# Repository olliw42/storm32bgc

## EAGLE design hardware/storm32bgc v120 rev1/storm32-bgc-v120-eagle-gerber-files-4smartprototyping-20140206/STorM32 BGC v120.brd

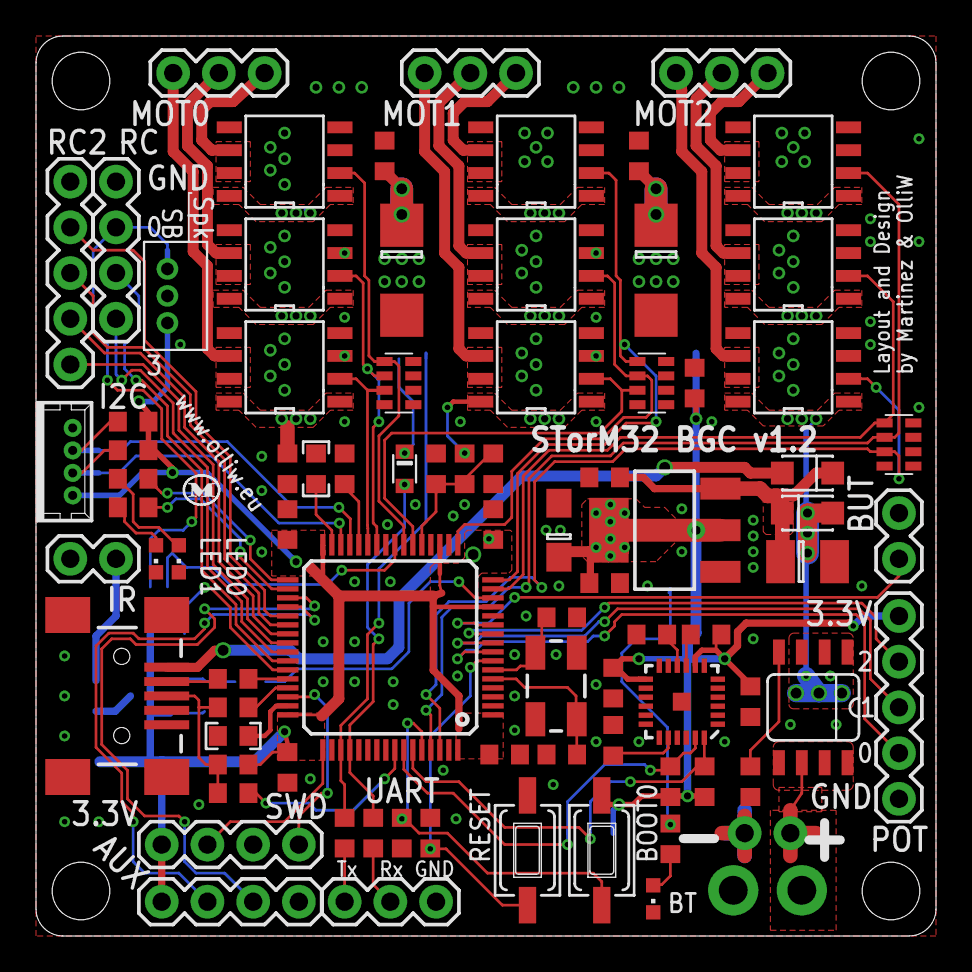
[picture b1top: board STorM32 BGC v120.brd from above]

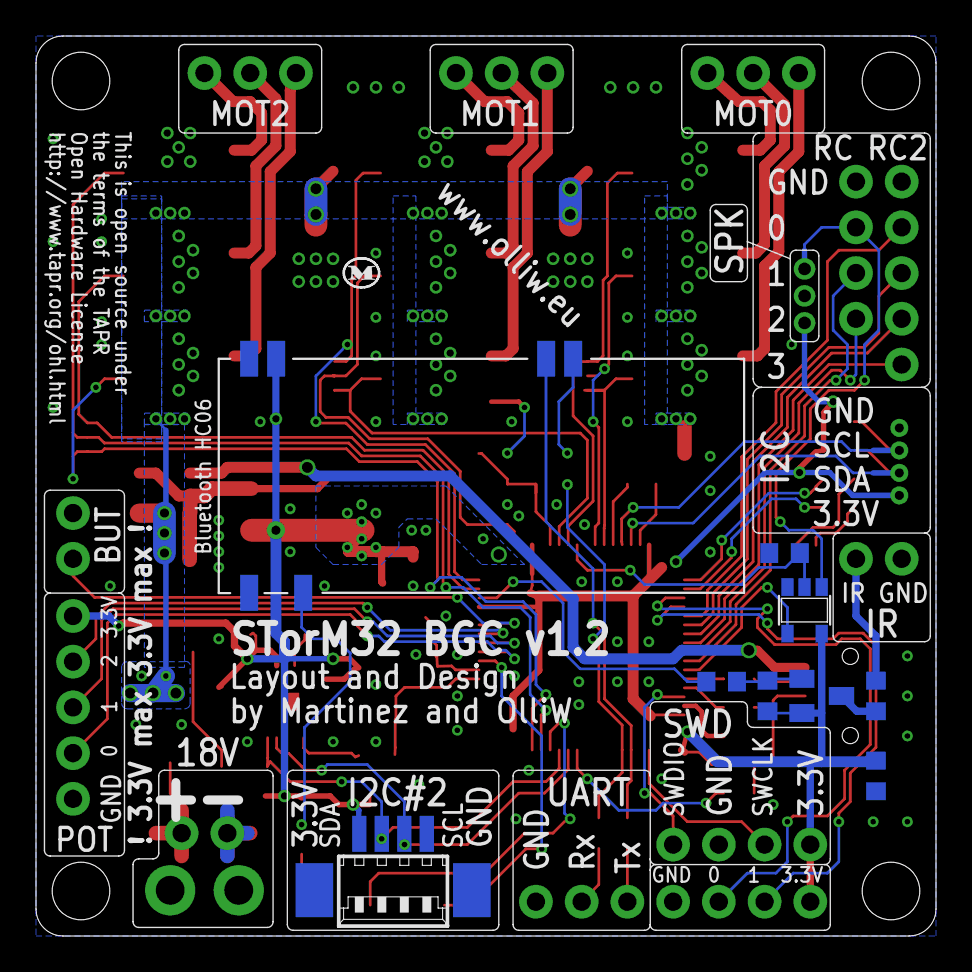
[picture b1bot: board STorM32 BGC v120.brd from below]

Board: 2 copper layers, 50.0 x 50.0 mm, 93 parts (9 on the bottom side), 77 nets.

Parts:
BAT+: 1X1_WITHOUT
BAT-: 1X1_WITHOUT
C1: 10u/20V; SMC_B
C2, C3, C5, C6, C7, C8, C11, C12, C15, C16, C17, C18, C19, C22, C23: 100n; C0603
C4: 10u/6.3V; SMC_A
C9, C10: 22p; C0603
C13, C14: 33u/20V; SMC_C
C20: 10n; C0603
C21: 2.2n; C0603
D1, D2: PMEG3010ER; SOD123W-DIODE
D3: 1PS76SB40; SOD110-R
IC1: STM32F103RCT6; TQFP64
IC2: NCP1117ST33T3G; SOT223
IC3, IC4, IC5, IC6, IC7, IC8, IC9, IC10, IC11: TC4452DFN08; DFN8
IC12: 74AHC1G86DBV; SOT23-5
IC13: MPU6050; QFN-24
IC14: BT HC06; BT_HC05_BASIC
JP1: USBMINIBSMD; USB-MINIB
JP2: MPU-I2C#1; 53047-04SMALL
JP3: SPK; B3B-ZR
JP4: I2C#2; MOLEX-53261-04-SMD-FLAT
JP5: SWD; 1X04
JP6: UART; 1X03
JP7: RC; 1X04
JP8: POT; 1X05
JP9: RC2; 1X05
JP10: BUT; 1X02
JP11: AUX; 1X04
JP12: MOT0; 1X03
JP13: MOT1; 1X03
JP14: MOT2; 1X03
JP15: IR; 1X02
LED1: green; CHIPLED_0603
LED2: red; CHIPLED_0603
LED3: yellow; CHIPLED_0603
Q1: 7B-8.000MAAJ-T; CRYTSAL-SMD-5X3
R1: 47k; R0603
R2, R3, R16, R17, R20: 10k; R0603
R4, R5: 0; R0603
R6: 1k; R0603
R7, R11, R12, R13, R14, R15, R19, R22, R23, R24, R25: 2.2k; R0603
R8, R9: 22; R0603
R10: 150; R0603
R18: 1.5k; R0603
R21: 47; R0603
RN1, RN2, RN3: 10k; CTS742C083
SW1, SW2: SW_TACT_3X6
T1: SI4835DDY; SO08
T2: BCX71HSMD; SOT23

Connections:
3.3V: C3.1, C4.+, C5.1, C6.1, C7.1, C8.1, C18.1, C19.1, C20.1, C23.1, IC1.1, IC1.13, IC1.19, IC1.32, IC1.48, IC1.64, IC2.2, IC2.4, IC12.5, IC13.8, IC13.13, IC14.12, JP2.1, JP3.1, JP4.1, JP5.4, JP8.5, JP11.4, R11.1, R14.2, R15.2, R20.2, R22.2, R23.2, R24.2, SW2.1, T2.2
A0: IC1.27, IC3.2, RN1.3
A1: IC1.22, IC6.2, RN2.3
A2: IC1.62, IC9.2, RN3.3
AUX0: IC1.35, JP11.2
AUX1: IC1.36, JP11.3
B0: IC1.26, IC4.2, RN1.2
B1: IC1.17, IC7.2, RN2.2
B2: IC1.15, IC10.2, RN3.1
BATP: BAT+.1, T1.5, T1.6, T1.7, T1.8
BOOT1: IC1.28, R3.2
BUT: IC1.11, JP10.2
C0: IC1.23, IC5.2, RN1.1
C1: IC1.16, IC8.2, RN2.1
C2: IC1.61, IC11.2, RN3.2
GND: BAT-.1, C1.-, C2.2, C3.2, C4.-, C5.2, C6.2, C7.2, C8.2, C9.1, C10.1, C11.2, C12.2, C13.-, C14.-, C15.2, C16.2, C17.2, C18.2, C19.2, C20.2, C21.2, C22.2, C23.2, IC1.12, IC1.18, IC1.63, IC2.1, IC3.3, IC3.4, IC3.5, IC4.3, IC4.4, IC4.5, IC5.3, IC5.4, IC5.5, IC6.3, IC6.4, IC6.5, IC7.3, IC7.4, IC7.5, IC8.3, IC8.4, IC8.5, IC9.3, IC9.4, IC9.5, IC10.3, IC10.4, IC10.5, IC11.3, IC11.4, IC11.5, IC12.3, IC13.1, IC13.11, IC13.18, IC14.13, IC14.22, JP1.GND, JP2.4, JP3.2, JP4.4, JP5.2, JP6.1, JP7.1, JP8.1, JP9.1, JP10.1, JP11.1, JP15.1, LED1.C, LED2.C, LED3.C, Q1.2, Q1.4, R1.2, R2.2, R3.1, R4.1, R5.1, R16.1, R18.1, RN1.5, RN1.6, RN1.7, RN1.8, RN2.5, RN2.6, RN2.7, RN2.8, RN3.5, RN3.6, RN3.7, RN3.8, SW1.2
IR: IC1.14, R19.1
LED0: IC1.33, R6.1
LED1: IC1.34, R7.1
LIPO: C12.1, IC1.21, R17.2, R18.2
M0A: IC3.6, IC3.7, JP12.1
M0B: IC4.6, IC4.7, JP12.2
M0C: IC5.6, IC5.7, JP12.3
M1A: IC6.6, IC6.7, JP13.1
M1B: IC7.6, IC7.7, JP13.2
M1C: IC8.6, IC8.7, JP13.3
M2A: IC9.6, IC9.7, JP14.1
M2B: IC10.6, IC10.7, JP14.2
M2C: IC11.6, IC11.7, JP14.3
unnamed: R21.1, T2.3
unnamed: JP15.2, R21.2
unnamed: C11.1, IC1.7, SW1.1
unnamed: IC1.60, R2.1, SW2.2
unnamed: LED1.A, R6.2
unnamed: LED2.A, R7.2
unnamed: IC1.47, R5.2
unnamed: C9.2, IC1.5, Q1.3
unnamed: C10.2, IC1.6, Q1.1
unnamed: JP1.D-, R8.1
unnamed: JP1.D+, R9.1, R10.1, R11.2
unnamed: IC13.9, R22.1
unnamed: C22.1, IC13.10
unnamed: IC14.24, R25.1
unnamed: LED3.A, R25.2
unnamed: R1.1, T1.4
unnamed: C21.1, IC13.20
unnamed: D3.C, IC14.1
unnamed: IC1.31, R4.2
unnamed: R19.2, R20.1, T2.1
unnamed: JP6.2, R13.2
unnamed: JP6.3, R12.2
POT0: IC1.8, JP8.2
POT1: IC1.9, JP8.3
POT2: IC1.10, JP8.4
RC0-IN: IC12.1, JP3.3, JP7.2
RC0/RX: IC1.43, IC12.4
RC1/TX: IC1.42, JP7.3
RC2: IC1.41, JP7.4
RC2-0: IC1.37, JP9.2
RC2-1: IC1.38, JP9.3
RC2-2: IC1.39, JP9.4
RC2-3: IC1.40, JP9.5
RX: D3.A, IC1.52, R13.1
SCL: IC1.29, JP2.3, R14.1
SCL#2: IC1.58, IC13.23, JP4.3, R23.1
SDA: IC1.30, JP2.2, R15.1
SDA#2: IC1.59, IC13.24, JP4.2, R24.1
SWCLK: IC1.49, JP5.3
SWDIO: IC1.46, JP5.1
TX: IC1.51, IC14.2, R12.1
USB-D: IC1.57, R10.2
USB-DM: IC1.44, R8.2
USB-DP: IC1.45, R9.2
VCC: C13.+, C14.+, C15.1, C16.1, C17.1, D1.A, IC3.1, IC3.8, IC4.1, IC4.8, IC5.1, IC5.8, IC6.1, IC6.8, IC7.1, IC7.8, IC8.1, IC8.8, IC9.1, IC9.8, IC10.1, IC10.8, IC11.1, IC11.8, R17.1, T1.1, T1.2, T1.3
VIN: C1.+, C2.1, D1.C, D2.C, IC2.3
VUSB: D2.A, JP1.VBUS
XOR: IC1.24, IC12.2, R16.2

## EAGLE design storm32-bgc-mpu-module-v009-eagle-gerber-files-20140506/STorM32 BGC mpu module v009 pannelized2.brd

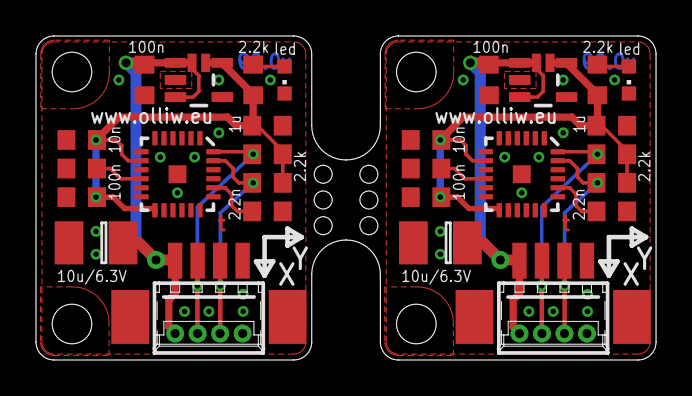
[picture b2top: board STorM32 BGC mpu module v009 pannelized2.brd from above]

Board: 2 copper layers, 34.4 x 18.0 mm, 30 parts (0 on the bottom side), 16 nets.

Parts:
C1, C8: 10u/6.3V; SMC_B
C2, C3, C6, C9, C12, C13: 100n; C0603
C4, C10: 10n; C0603
C5, C11: 2.2n; C0603
C7, C14: 1u; C0603
IC1, IC3: MPU6050; QFN-24
IC2, IC4: SOT23-5
JP1, JP2: I2C#2; MOLEX-53261-04-SMD-BOTH
LED1, LED2: red; CHIPLED_0603
R1, R2, R3, R4, R5, R6: 2.2k; R0603
SJ1, SJ2: SOLDERJUMPERNO; SJ_2S-NO

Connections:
3.3V: C3.1, C4.1, C7.1, IC1.8, IC1.13, IC2.5, R1.1, R2.2, R3.2, SJ1.2
3.3V1: C10.1, C12.1, C14.1, IC3.8, IC3.13, IC4.5, R4.2, R5.2, R6.1, SJ2.2
5V: C1.+, C2.1, IC2.1, IC2.3, JP1.1, JP1.5, SJ1.1
5V1: C8.+, C13.1, IC4.1, IC4.3, JP2.1, JP2.5, SJ2.1
GND: C1.-, C2.2, C3.2, C4.2, C5.2, C6.2, C7.2, IC1.1, IC1.9, IC1.11, IC1.18, IC2.2, IC2.4, JP1.4, JP1.8, LED1.C
GND4: C8.-, C9.2, C10.2, C11.2, C12.2, C13.2, C14.2, IC3.1, IC3.9, IC3.11, IC3.18, IC4.2, IC4.4, JP2.4, JP2.8, LED2.C
unnamed: LED2.A, R6.2
unnamed: C9.1, IC3.10
unnamed: C11.1, IC3.20
unnamed: LED1.A, R1.2
unnamed: C6.1, IC1.10
unnamed: C5.1, IC1.20
SCL: IC1.23, JP1.3, JP1.7, R2.1
SCL1: IC3.23, JP2.3, JP2.7, R4.1
SDA: IC1.24, JP1.2, JP1.6, R3.1
SDA1: IC3.24, JP2.2, JP2.6, R5.1

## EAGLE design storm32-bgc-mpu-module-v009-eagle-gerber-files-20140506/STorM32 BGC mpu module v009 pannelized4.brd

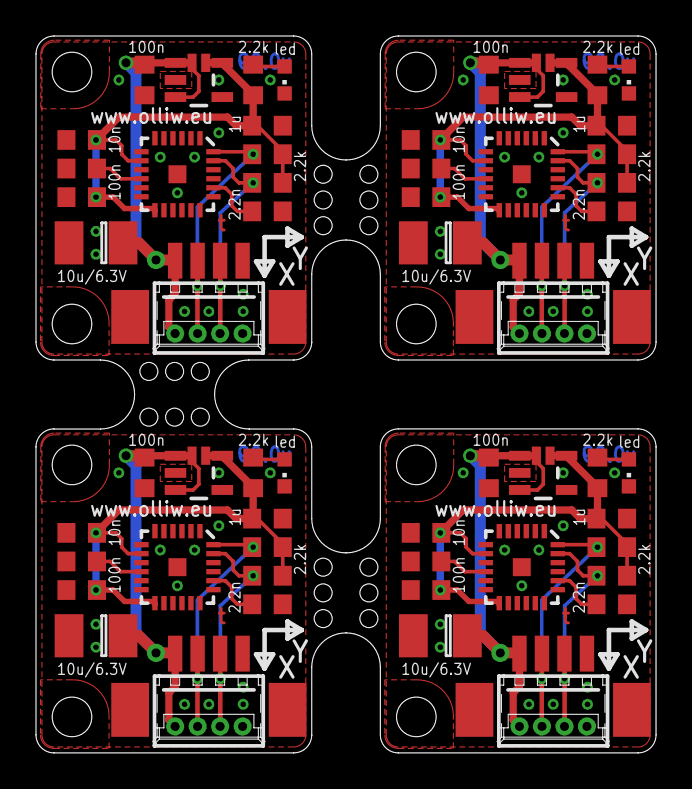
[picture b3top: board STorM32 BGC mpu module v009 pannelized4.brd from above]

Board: 2 copper layers, 34.4 x 39.8 mm, 60 parts (0 on the bottom side), 32 nets.

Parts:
C1, C8, C15, C22: 10u/6.3V; SMC_B
C2, C3, C6, C9, C12, C13, C16, C19, C20, C23, C26, C27: 100n; C0603
C4, C10, C17, C24: 10n; C0603
C5, C11, C18, C25: 2.2n; C0603
C7, C14, C21, C28: 1u; C0603
IC1, IC3, IC5, IC7: MPU6050; QFN-24
IC2, IC4, IC6, IC8: SOT23-5
JP1, JP2, JP3, JP4: I2C#2; MOLEX-53261-04-SMD-BOTH
LED1, LED2, LED3, LED4: red; CHIPLED_0603
R1, R2, R3, R4, R5, R6, R7, R8, R9, R10, R11, R12: 2.2k; R0603
SJ1, SJ2, SJ3, SJ4: SOLDERJUMPERNO; SJ_2S-NO

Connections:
3.3V: C3.1, C4.1, C7.1, IC1.8, IC1.13, IC2.5, R1.1, R2.2, R3.2, SJ1.2
3.3V1: C10.1, C12.1, C14.1, IC3.8, IC3.13, IC4.5, R4.2, R5.2, R6.1, SJ2.2
3.3V2: C17.1, C19.1, C21.1, IC5.8, IC5.13, IC6.5, R7.2, R8.2, R9.1, SJ3.2
3.3V3: C24.1, C26.1, C28.1, IC7.8, IC7.13, IC8.5, R10.2, R11.2, R12.1, SJ4.2
5V: C1.+, C2.1, IC2.1, IC2.3, JP1.1, JP1.5, SJ1.1
5V1: C8.+, C13.1, IC4.1, IC4.3, JP2.1, JP2.5, SJ2.1
5V2: C15.+, C20.1, IC6.1, IC6.3, JP3.1, JP3.5, SJ3.1
5V3: C22.+, C27.1, IC8.1, IC8.3, JP4.1, JP4.5, SJ4.1
GND: C1.-, C2.2, C3.2, C4.2, C5.2, C6.2, C7.2, IC1.1, IC1.9, IC1.11, IC1.18, IC2.2, IC2.4, JP1.4, JP1.8, LED1.C
GND4: C8.-, C9.2, C10.2, C11.2, C12.2, C13.2, C14.2, IC3.1, IC3.9, IC3.11, IC3.18, IC4.2, IC4.4, JP2.4, JP2.8, LED2.C
GND5: C15.-, C16.2, C17.2, C18.2, C19.2, C20.2, C21.2, IC5.1, IC5.9, IC5.11, IC5.18, IC6.2, IC6.4, JP3.4, JP3.8, LED3.C
GND6: C22.-, C23.2, C24.2, C25.2, C26.2, C27.2, C28.2, IC7.1, IC7.9, IC7.11, IC7.18, IC8.2, IC8.4, JP4.4, JP4.8, LED4.C
unnamed: LED2.A, R6.2
unnamed: C9.1, IC3.10
unnamed: C11.1, IC3.20
unnamed: LED3.A, R9.2
unnamed: C16.1, IC5.10
unnamed: C18.1, IC5.20
unnamed: LED4.A, R12.2
unnamed: C23.1, IC7.10
unnamed: LED1.A, R1.2
unnamed: C25.1, IC7.20
unnamed: C6.1, IC1.10
unnamed: C5.1, IC1.20
SCL: IC1.23, JP1.3, JP1.7, R2.1
SCL1: IC3.23, JP2.3, JP2.7, R4.1
SCL2: IC5.23, JP3.3, JP3.7, R7.1
SCL3: IC7.23, JP4.3, JP4.7, R10.1
SDA: IC1.24, JP1.2, JP1.6, R3.1
SDA1: IC3.24, JP2.2, JP2.6, R5.1
SDA2: IC5.24, JP3.2, JP3.6, R8.1
SDA3: IC7.24, JP4.2, JP4.6, R11.1

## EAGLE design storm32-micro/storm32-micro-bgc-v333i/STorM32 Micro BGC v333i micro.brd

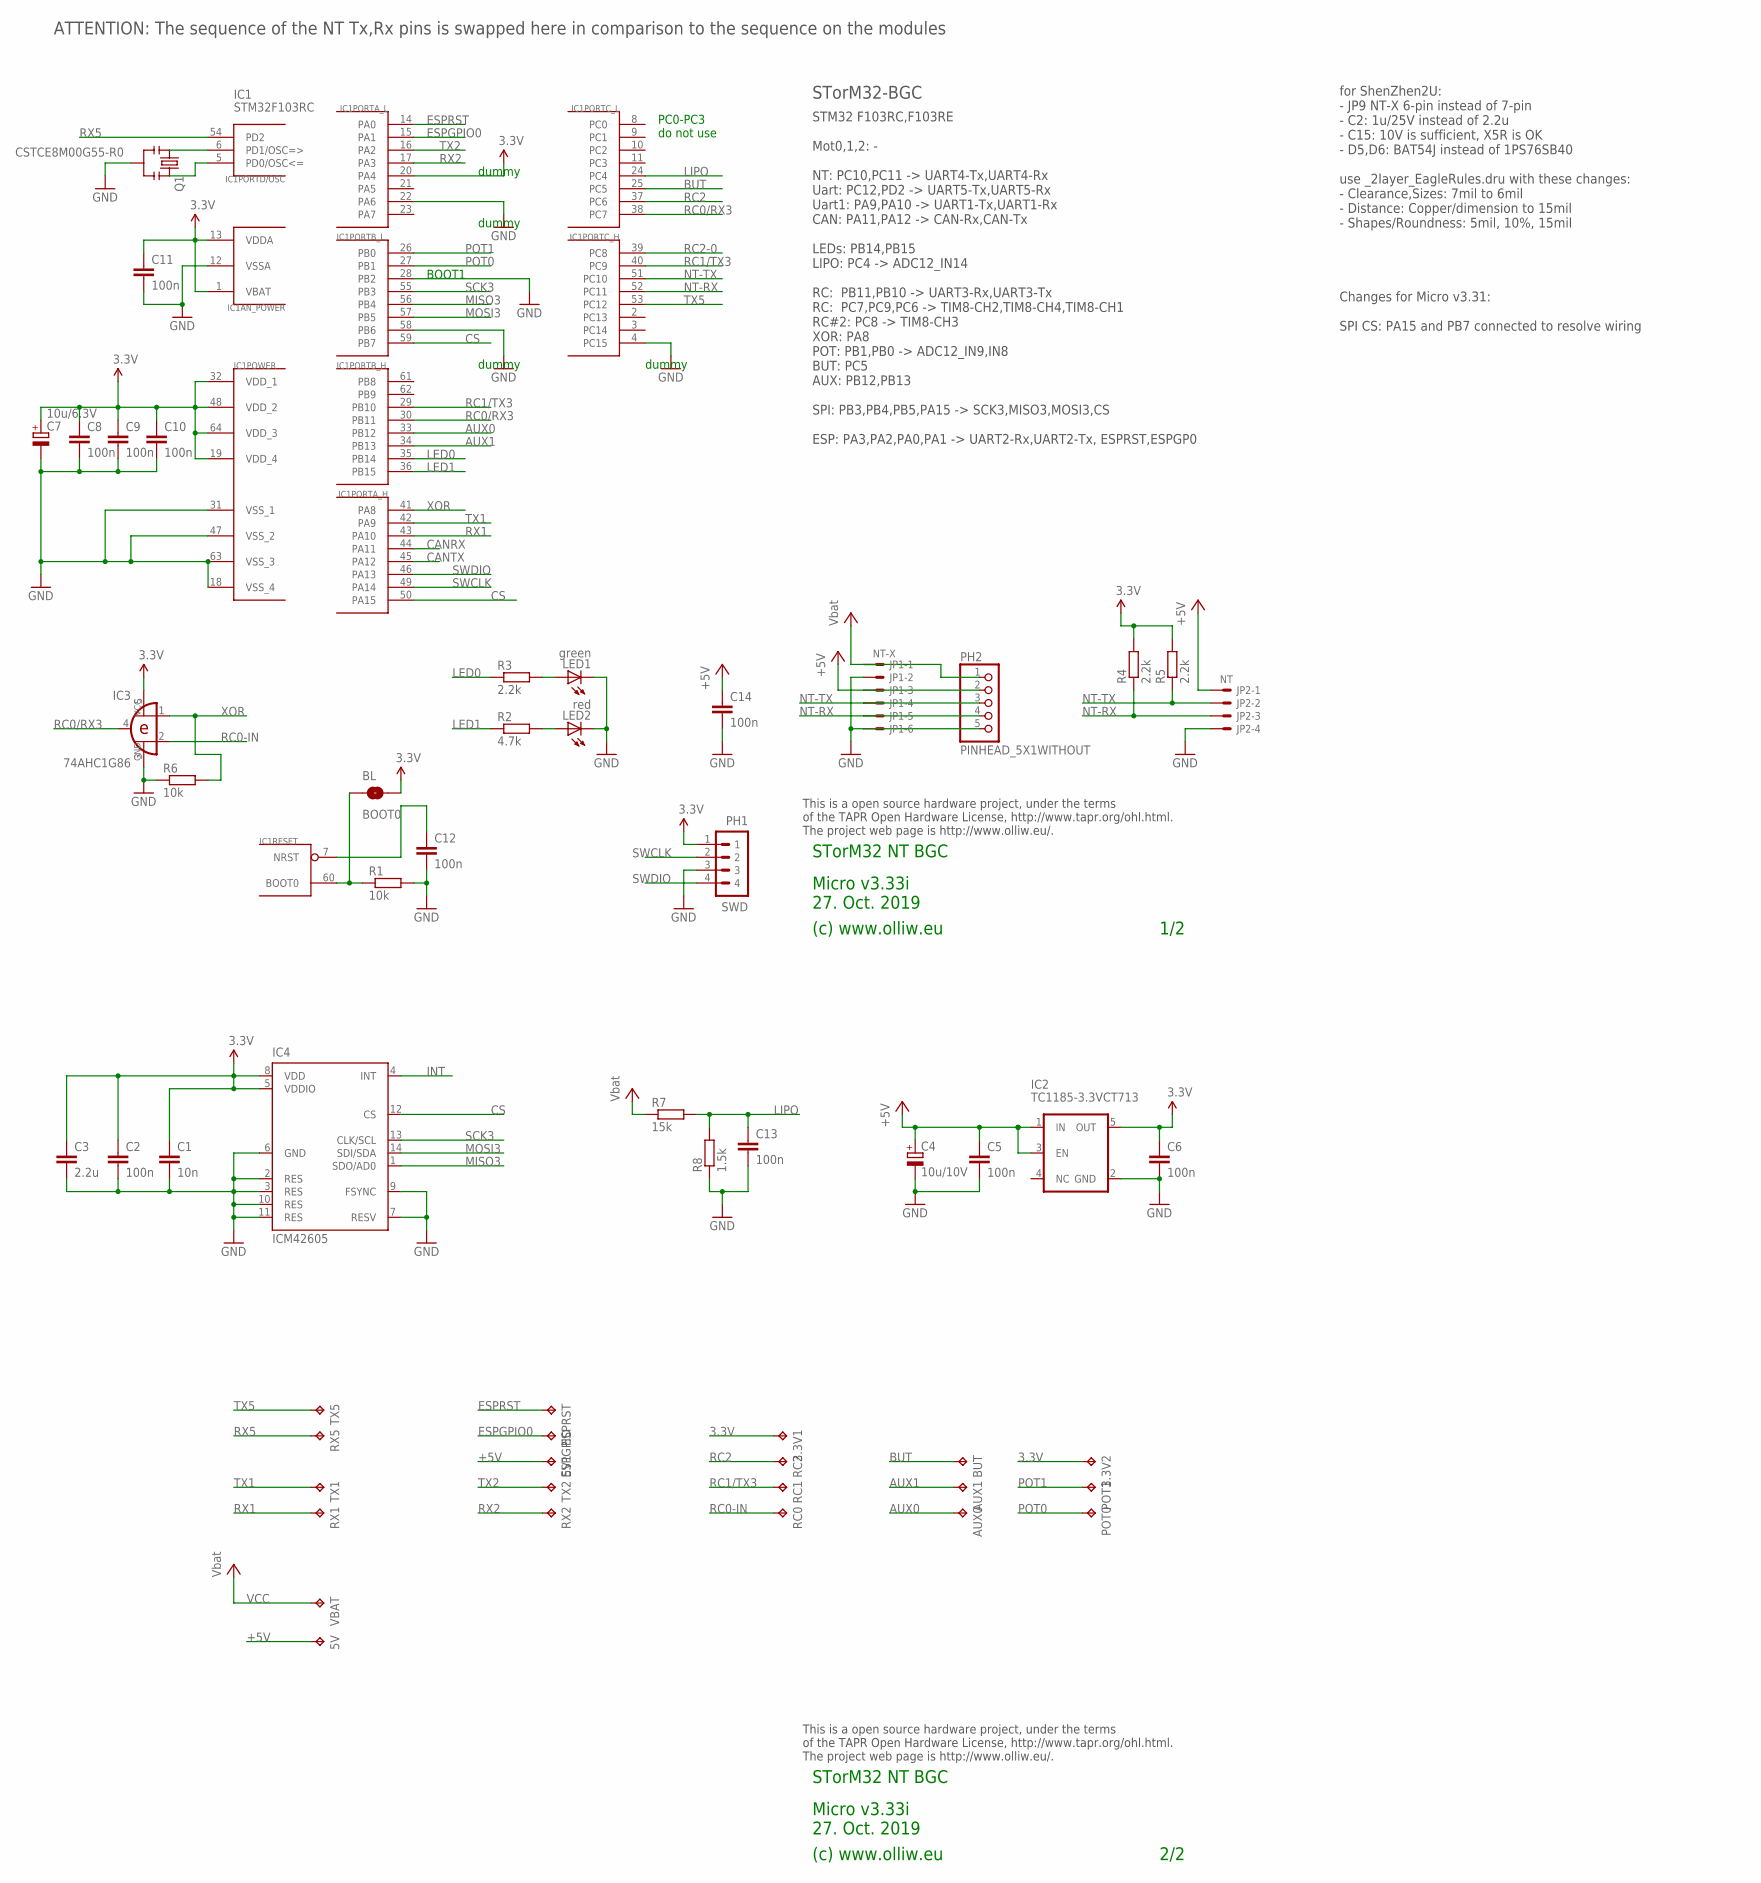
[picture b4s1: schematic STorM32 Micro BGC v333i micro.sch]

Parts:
3.3V1, 3.3V2, 5V, 5V1: TPB1,27; B1,27
AUX0, AUX1: TPB1,27; B1,27
BL: BOOT0; SJ_2S-NO
BUT: TPB1,27; B1,27
C1: 10n; C0402
C2, C6, C8, C9, C10, C11, C12, C13, C14: 100n; C0402
C3: 2.2u; C0603
C4: 10u/10V; SMC_A
C5: 100n; C0603
C7: 10u/6.3V; SMC_A
ESPGPIO: TPB1,27; B1,27
ESPRST: TPB1,27; B1,27
IC1: STM32F103RCT6; TQFP64
IC2: TC1185-3.3VCT713; SOT23-5
IC3: 74AHC1G86; SOT23-5-VER1
IC4: ICM42605; LGA14-2.5X3
JP1: NT-X; SM06B-SRSS-TB
JP2: NT; SM04B-SRSS-TB
LED1: green; CHIPLED_0603
LED2: red; CHIPLED_0603
PH1: SWD; 4X1_1P27_OCT_BILEX
PH2: PINHEAD_5X1WITHOUT; PINHEAD_5X1_WO
POT0, POT1: TPB1,27; B1,27
Q1: CSTCE8M00G55-R0; RESONATOR-SMD
R1, R6: 10k; R0402
R2: 4.7k; R0402
R3, R4, R5: 2.2k; R0402
R7: 15k; R0402
R8: 1.5k; R0402
RC0, RC1, RC2: TPB1,27; B1,27
RX1, RX2, RX5: TPB1,27; B1,27
TX1, TX2, TX5: TPB1,27; B1,27
VBAT: TPB1,27; B1,27

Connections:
3.3V: 3.3V1.TP, 3.3V2.TP, BL.2, C1.1, C2.1, C3.1, C6.1, C7.+, C8.1, C9.1, C10.1, C11.1, IC1.1 (VBAT), IC1.13 (VDDA), IC1.19 (VDD_4), IC1.20 (PA4), IC1.32 (VDD_1), IC1.48 (VDD_2), IC1.64 (VDD_3), IC2.5 (OUT), IC3.5 (VCC), IC4.5 (VDDIO), IC4.8 (VDD), PH1.1, R4.2, R5.2
+5V: 5V.TP, 5V1.TP, C4.+, C5.1, C14.1, IC2.1 (IN), IC2.3 (EN), JP1.3, JP2.1, PH2.2
AUX0: AUX0.TP, IC1.33 (PB12)
AUX1: AUX1.TP, IC1.34 (PB13)
BOOT0: BL.1, IC1.60 (BOOT0), R1.1
BUT: BUT.TP, IC1.25 (PC5)
CANRX: IC1.44 (PA11)
CANTX: IC1.45 (PA12)
CS: IC1.50 (PA15), IC1.59 (PB7), IC4.12 (CS)
ESPGPIO0: ESPGPIO.TP, IC1.15 (PA1)
ESPRST: ESPRST.TP, IC1.14 (PA0)
GND: C1.2, C2.2, C3.2, C4.-, C5.2, C6.2, C7.-, C8.2, C9.2, C10.2, C11.2, C12.2, C13.2, C14.2, IC1.4 (PC15), IC1.12 (VSSA), IC1.18 (VSS_4), IC1.22 (PA6), IC1.28 (PB2), IC1.31 (VSS_1), IC1.47 (VSS_2), IC1.58 (PB6), IC1.63 (VSS_3), IC2.2 (GND), IC3.3 (GND), IC4.2 (RES), IC4.3 (RES), IC4.6 (GND), IC4.7 (RESV), IC4.9 (FSYNC), IC4.10 (RES), IC4.11 (RES), JP1.2, JP1.6, JP2.4, LED1.C, LED2.C, PH1.3, PH2.5, Q1.2, R1.2, R6.1, R8.1
INT: IC4.4 (INT)
LED0: IC1.35 (PB14), R3.1
LED1: IC1.36 (PB15), R2.1
LIPO: C13.1, IC1.24 (PC4), R7.2, R8.2
MISO3: IC1.56 (PB4), IC4.1 (SDO/AD0)
MOSI3: IC1.57 (PB5), IC4.14 (SDI/SDA)
unnamed: LED1.A, R3.2
unnamed: LED2.A, R2.2
unnamed: IC1.5 (PD0/OSC<=), Q1.3
unnamed: IC1.6 (PD1/OSC=>), Q1.1
NRST: C12.1, IC1.7 (NRST)
NT-RX: IC1.52 (PC11), JP1.5, JP2.3, PH2.4, R4.1
NT-TX: IC1.51 (PC10), JP1.4, JP2.2, PH2.3, R5.1
POT0: IC1.27 (PB1), POT0.TP
POT1: IC1.26 (PB0), POT1.TP
RC0-IN: IC3.2 (I1), RC0.TP
RC0/RX3: IC1.30 (PB11), IC1.38 (PC7), IC3.4 (O)
RC1/TX3: IC1.29 (PB10), IC1.40 (PC9), RC1.TP
RC2: IC1.37 (PC6), RC2.TP
RC2-0: IC1.39 (PC8)
RX1: IC1.43 (PA10), RX1.TP
RX2: IC1.17 (PA3), RX2.TP
RX5: IC1.54 (PD2), RX5.TP
SCK3: IC1.55 (PB3), IC4.13 (CLK/SCL)
SWCLK: IC1.49 (PA14), PH1.2
SWDIO: IC1.46 (PA13), PH1.4
TX1: IC1.42 (PA9), TX1.TP
TX2: IC1.16 (PA2), TX2.TP
TX5: IC1.53 (PC12), TX5.TP
VCC: JP1.1, PH2.1, R7.1, VBAT.TP
XOR: IC1.41 (PA8), IC3.1 (I0), R6.2

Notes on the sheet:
(c) www.olliw.eu
STorM32 NT BGC
This is a open source hardware project, under the terms of the TAPR Open Hardware License, http://www.tapr.org/ohl.html. The project web page is http://www.olliw.eu/.
STM32 F103RC,F103RE Mot0,1,2: - NT: PC10,PC11 -> UART4-Tx,UART4-Rx Uart: PC12,PD2 -> UART5-Tx,UART5-Rx Uart1: PA9,PA10 -> UART1-Tx,UART1-Rx CAN: PA11,PA12 -> CAN-Rx,CAN-Tx LEDs: PB14,PB15 LIPO: PC4 -> ADC12_IN14 RC: PB11,PB10 -> UART3-Rx,UART3-Tx RC: PC7,PC9,PC6 -> TIM8-CH2,TIM8-CH4,TIM8-CH1 RC#2: 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
Micro v3.33i 27. Oct. 2019
STM32F103RC
STorM32-BGC
1/2
2/2
IC1
ATTENTION: The sequence of the NT Tx,Rx pins is swapped here in comparison to the sequence on the modules
BOOT1
dummy
PC0-PC3 do not use
for ShenZhen2U: - JP9 NT-X 6-pin instead of 7-pin - C2: 1u/25V instead of 2.2u - C15: 10V is sufficient, X5R is OK - D5,D6: BAT54J instead of 1PS76SB40 use _2layer_EagleRules.dru with these changes: - Clearance,Sizes: 7mil to 6mil - Distance: Copper/dimension to 15mil - Shapes/Roundness: 5mil, 10%,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
Changes for Micro v3.31: SPI CS: PA15 and PB7 connected to resolve wiring

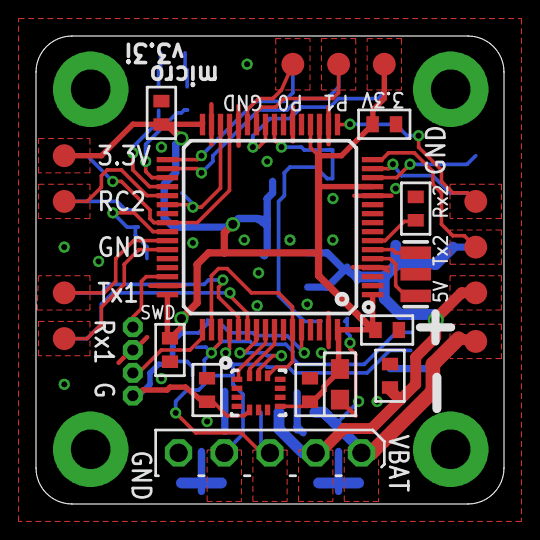
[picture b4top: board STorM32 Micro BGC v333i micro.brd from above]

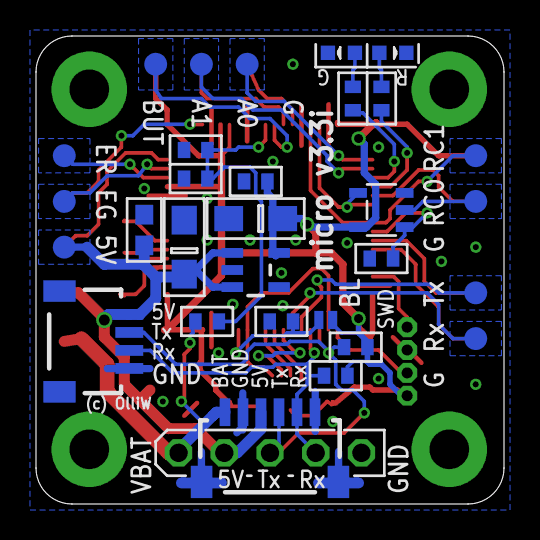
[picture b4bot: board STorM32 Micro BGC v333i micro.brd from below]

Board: 2 copper layers, 26.0 x 26.0 mm, 55 parts (30 on the bottom side), 39 nets.

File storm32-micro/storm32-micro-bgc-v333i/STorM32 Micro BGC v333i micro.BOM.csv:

"Part";"Value";"Device";"Package";"Description";"TP_SIGNAL_NAME";
"3.3V1";"TPB1,27";"TPB1,27";"B1,27";"Test pad";"";
"3.3V2";"TPB1,27";"TPB1,27";"B1,27";"Test pad";"";
"5V";"TPB1,27";"TPB1,27";"B1,27";"Test pad";"";
"5V1";"TPB1,27";"TPB1,27";"B1,27";"Test pad";"";
"AUX0";"TPB1,27";"TPB1,27";"B1,27";"Test pad";"";
"AUX1";"TPB1,27";"TPB1,27";"B1,27";"Test pad";"";
"BL";"BOOT0";"SOLDERJUMPERNO";"SJ_2S-NO";"Solder Jumper";"";
"BUT";"TPB1,27";"TPB1,27";"B1,27";"Test pad";"";
"C1";"10n";"C-EUC0402";"C0402";"CAPACITOR, European symbol";"";
"C2";"100n";"C-EUC0402";"C0402";"CAPACITOR, European symbol";"";
"C3";"2.2u";"C-EUC0603";"C0603";"CAPACITOR, European symbol";"";
"C4";"10u/10V";"CPOL-EUSMCA";"SMC_A";"POLARIZED CAPACITOR, European symbol";"";
"C5";"100n";"C-EUC0603";"C0603";"CAPACITOR, European symbol";"";
"C6";"100n";"C-EUC0402";"C0402";"CAPACITOR, European symbol";"";
"C7";"10u/6.3V";"CPOL-EUSMCA";"SMC_A";"POLARIZED CAPACITOR, European symbol";"";
"C8";"100n";"C-EUC0402";"C0402";"CAPACITOR, European symbol";"";
"C9";"100n";"C-EUC0402";"C0402";"CAPACITOR, European symbol";"";
"C10";"100n";"C-EUC0402";"C0402";"CAPACITOR, European symbol";"";
"C11";"100n";"C-EUC0402";"C0402";"CAPACITOR, European symbol";"";
"C12";"100n";"C-EUC0402";"C0402";"CAPACITOR, European symbol";"";
"C13";"100n";"C-EUC0402";"C0402";"CAPACITOR, European symbol";"";
"C14";"100n";"C-EUC0402";"C0402";"CAPACITOR, European symbol";"";
"ESPGPIO";"TPB1,27";"TPB1,27";"B1,27";"Test pad";"";
"ESPRST";"TPB1,27";"TPB1,27";"B1,27";"Test pad";"";
"IC1";"STM32F103RCT6";"STM32F10XRXT6";"TQFP64";"STM32F101/103 64pin LQFP";"";
"IC2";"TC1185-3.3VCT713";"V_REG_TPS76433SOT23-5";"SOT23-5";"Voltage Regulator";"";
"IC3";"74AHC1G86";"74AHC1G86";"SOT23-5-VER1";"";"";
"IC4";"ICM42605";"ICM42605";"LGA14-2.5X3";"";"";
"JP1";"NT-X";"SM06B-SRSS-TB";"SM06B-SRSS-TB";"Disconnectable Crimp style connector, 1.0mm pitch6 contacts";"";
"JP2";"NT";"SM04B-SRSS-TB";"SM04B-SRSS-TB";"Disconnectable Crimp style connector, 1.0mm pitch4 contacts";"";
"LED1";"green";"LEDCHIPLED_0603";"CHIPLED_0603";"LED";"";
"LED2";"red";"LEDCHIPLED_0603";"CHIPLED_0603";"LED";"";
"PH1";"SWD";"P4X1_1P27-OCT_BILEX";"4X1_1P27_OCT_BILEX";"";"";
"PH2";"PINHEAD_5X1WITHOUT";"PINHEAD_5X1WITHOUT";"PINHEAD_5X1_WO";"";"";
"POT0";"TPB1,27";"TPB1,27";"B1,27";"Test pad";"";
"POT1";"TPB1,27";"TPB1,27";"B1,27";"Test pad";"";
"Q1";"CSTCE8M00G55-R0";"RESONATORSMD";"RESONATOR-SMD";"Resonator";"";
"R1";"10k";"R-EU_R0402";"R0402";"RESISTOR, European symbol";"";
"R2";"4.7k";"R-EU_R0402";"R0402";"RESISTOR, European symbol";"";
"R3";"2.2k";"R-EU_R0402";"R0402";"RESISTOR, European symbol";"";
"R4";"2.2k";"R-EU_R0402";"R0402";"RESISTOR, European symbol";"";
"R5";"2.2k";"R-EU_R0402";"R0402";"RESISTOR, European symbol";"";
"R6";"10k";"R-EU_R0402";"R0402";"RESISTOR, European symbol";"";
"R7";"15k";"R-EU_R0402";"R0402";"RESISTOR, European symbol";"";
"R8";"1.5k";"R-EU_R0402";"R0402";"RESISTOR, European symbol";"";
"RC0";"TPB1,27";"TPB1,27";"B1,27";"Test pad";"";
"RC1";"TPB1,27";"TPB1,27";"B1,27";"Test pad";"";
"RC2";"TPB1,27";"TPB1,27";"B1,27";"Test pad";"";
"RX1";"TPB1,27";"TPB1,27";"B1,27";"Test pad";"";
"RX2";"TPB1,27";"TPB1,27";"B1,27";"Test pad";"";
"RX5";"TPB1,27";"TPB1,27";"B1,27";"Test pad";"";
"TX1";"TPB1,27";"TPB1,27";"B1,27";"Test pad";"";
"TX2";"TPB1,27";"TPB1,27";"B1,27";"Test pad";"";
"TX5";"TPB1,27";"TPB1,27";"B1,27";"Test pad";"";
"VBAT";"TPB1,27";"TPB1,27";"B1,27";"Test pad";"";

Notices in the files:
parts and their libraries:
Licensing: CC v3.0 Share-Alike You are welcome to use this library for commercial purposes.
